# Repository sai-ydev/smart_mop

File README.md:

# Bluetooth-Enabled Smart Mop using the PSOC BLE pioneer kit

A Bluetooth enabled smart mop that tracks liquid refill levels using CapSense Technology.

A detailed writeup is available from [here](https://www.hackster.io/yamanoorsai/bluetooth-enabled-smart-mop-using-the-psoc-ble-pioneer-kit-8d9399).

## Folder structure

1. SmartMop.cydsn - Project workspace for smart mop
2. hardware - PCB design files, Gerbers, and BoM

# Videos

Mobile App Demo

Power Profiling Demo

Smart Mop Demo

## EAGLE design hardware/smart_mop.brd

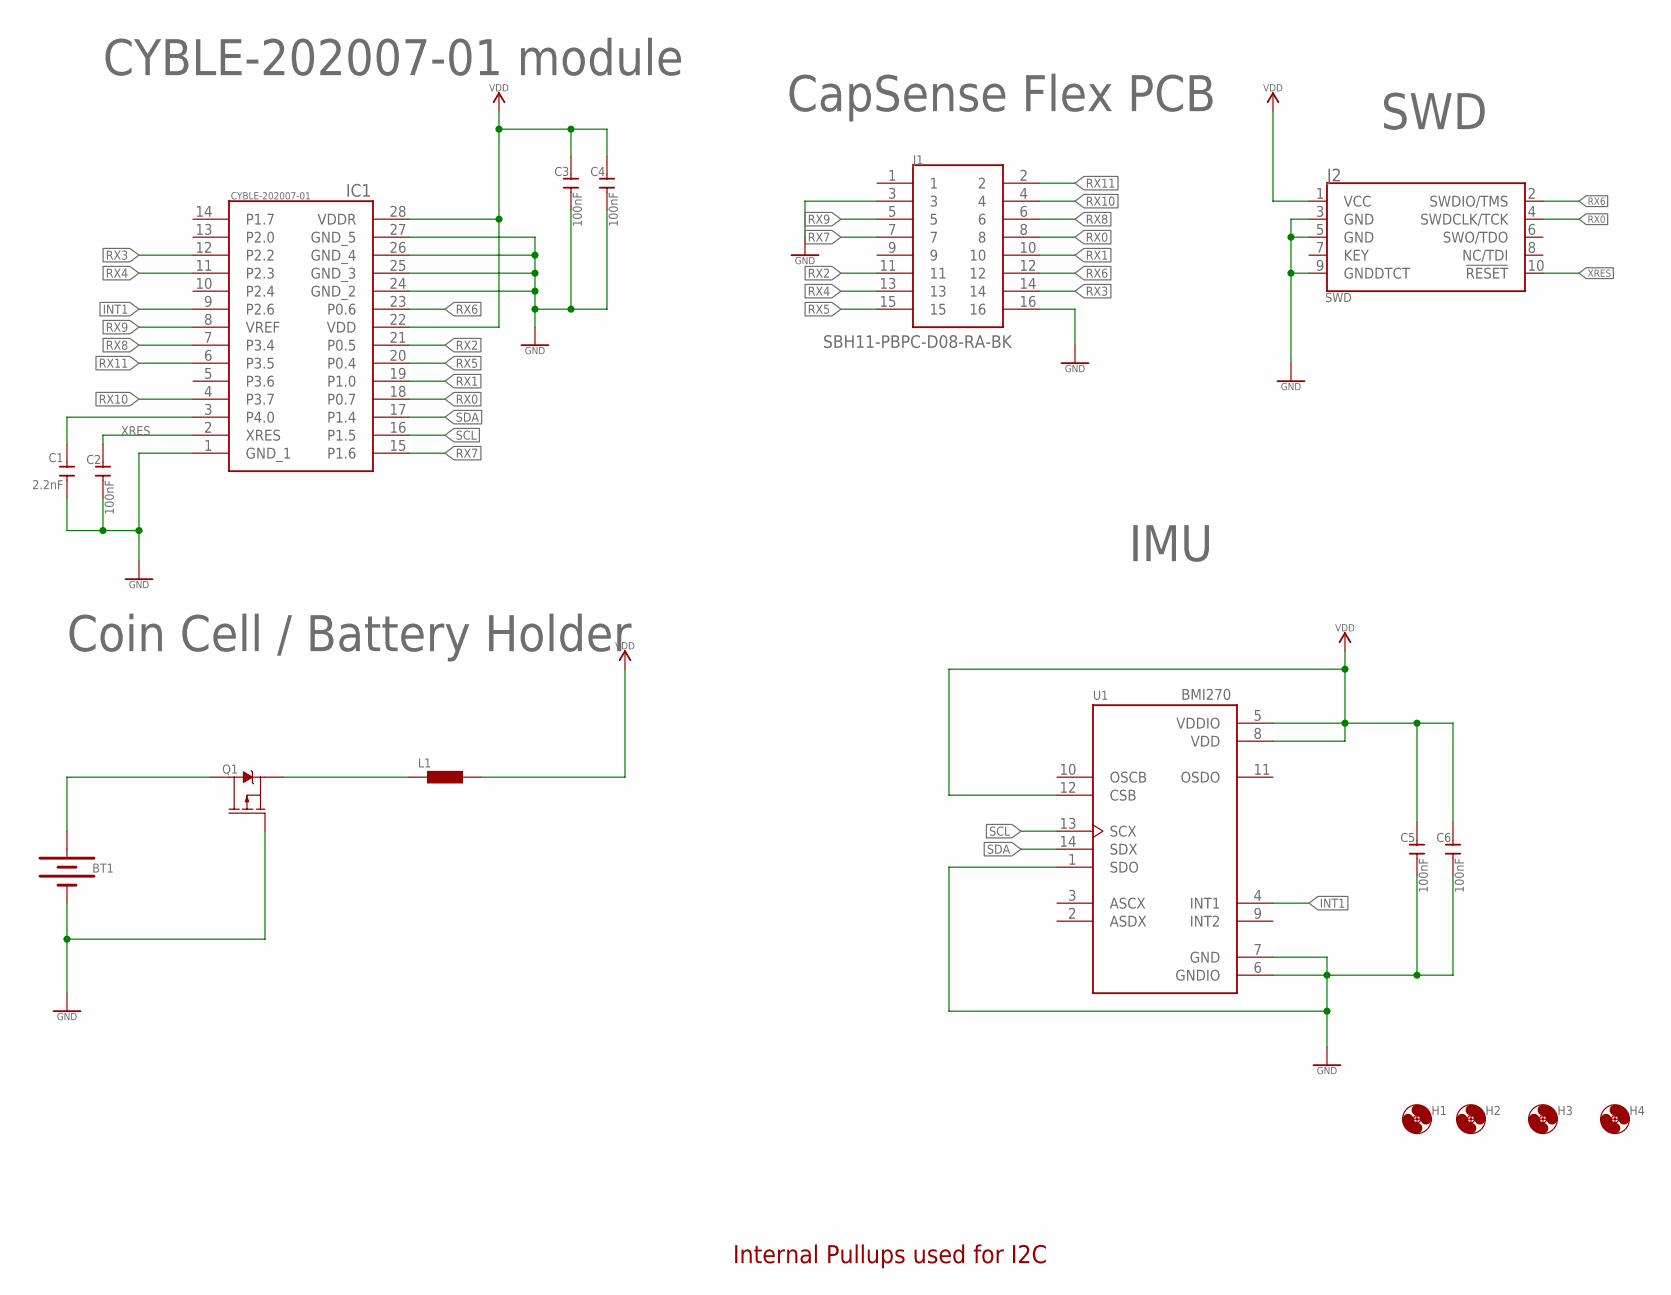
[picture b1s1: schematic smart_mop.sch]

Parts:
BT1: BATTERY-20MM_SMD; BATTCON_20MM
C1: 2.2nF; C0402
C2, C3, C4, C5, C6: 100nF; C0402
H1, H2, H3, H4: MOUNT-HOLE2.8; 2,8
IC1: CYBLE-202007-01; CYBLE20200701
J1: SBH11-PBPC-D08-RA-BK; SHDRRA16W64P254_2X8_2782X910X9
J2: SWD; SAMTECH_FTSH-105-01
L1: BLM15HB121SN1; 0402
Q1: 2.5A/30V/105mΩ; SOT23-3
U1: BMI270; XDCR_BMI270

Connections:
GND: BT1.2 (-), C1.1, C2.1, C3.1, C4.1, C5.1, C6.1, IC1.1 (GND_1), IC1.24 (GND_2), IC1.25 (GND_3), IC1.26 (GND_4), IC1.27 (GND_5), J1.3, J1.16, J2.3 (GND), J2.5 (GND), J2.9 (GNDDTCT), Q1.1 (G), U1.1 (SDO), U1.6 (GNDIO), U1.7 (GND)
INT1: IC1.9 (P2.6), U1.4 (INT1)
unnamed: BT1.1 (+), Q1.3 (D)
unnamed: C1.2, IC1.3 (P4.0)
unnamed: L1.1, Q1.2 (S)
RX0: IC1.18 (P0.7), J1.8, J2.4 (SWDCLK/TCK)
RX1: IC1.19 (P1.0), J1.10
RX2: IC1.21 (P0.5), J1.11
RX3: IC1.12 (P2.2), J1.14
RX4: IC1.11 (P2.3), J1.13
RX5: IC1.20 (P0.4), J1.15
RX6: IC1.23 (P0.6), J1.12, J2.2 (SWDIO/TMS)
RX7: IC1.15 (P1.6), J1.7
RX8: IC1.7 (P3.4), J1.6
RX9: IC1.8 (VREF), J1.5
RX10: IC1.4 (P3.7), J1.4
RX11: IC1.6 (P3.5), J1.2
SCL: IC1.16 (P1.5), U1.13 (SCX)
SDA: IC1.17 (P1.4), U1.14 (SDX)
VDD: C3.2, C4.2, C5.2, C6.2, IC1.22 (VDD), IC1.28 (VDDR), J2.1 (VCC), L1.2, U1.5 (VDDIO), U1.8 (VDD), U1.12 (CSB)
XRES: C2.2, IC1.2 (XRES), J2.10 (!RESET)

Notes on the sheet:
Coin Cell / Battery Holder
CYBLE-202007-01 module
CapSense Flex PCB
IMU
Internal Pullups used for I2C
SWD

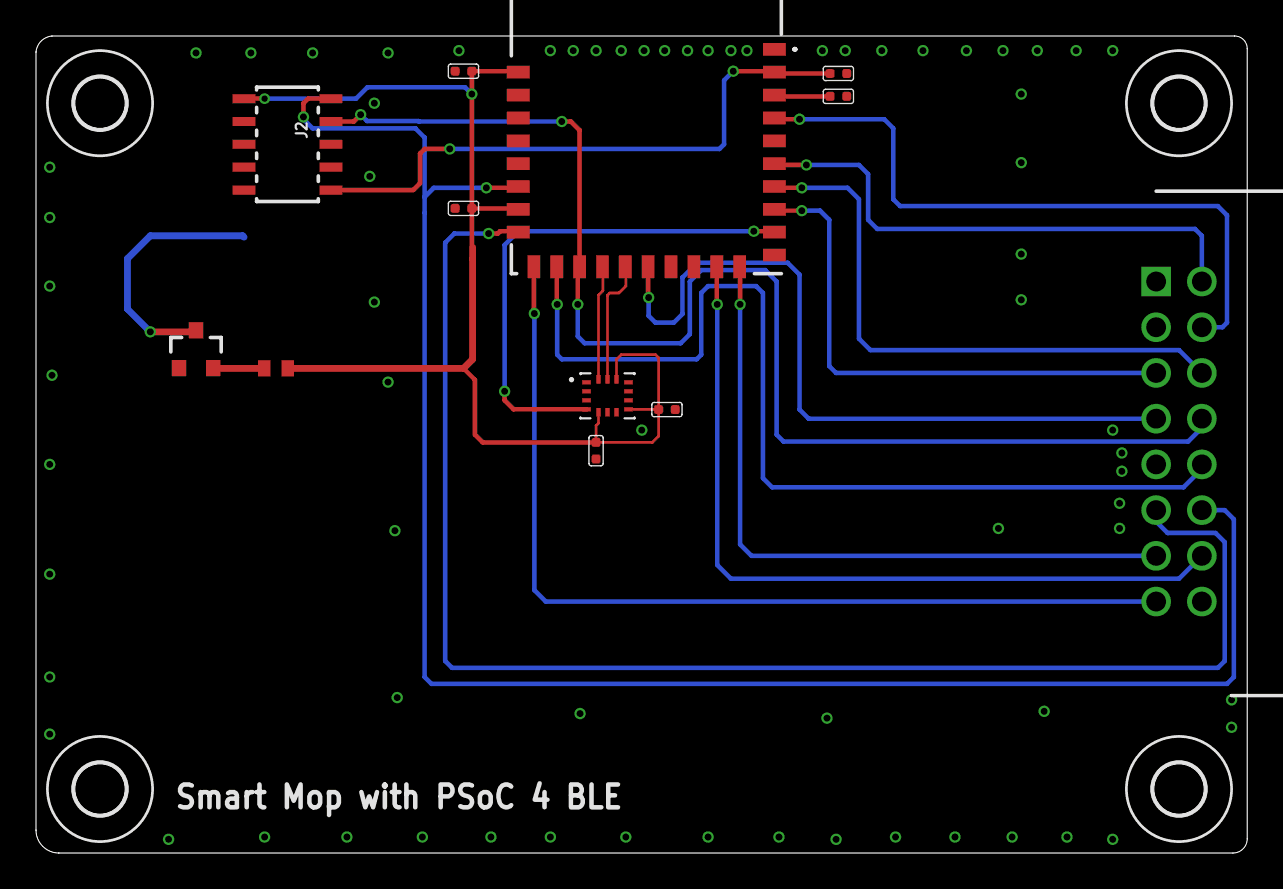
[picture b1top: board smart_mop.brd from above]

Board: 2 copper layers, 67.3 x 45.4 mm, 17 parts (1 on the bottom side), 21 nets.

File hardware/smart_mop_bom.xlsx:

Part | Value | MPN | Cost (USD)
BT1 |  | BATTERY-20MM_SMD | 0.76
C1 | 2.2nF | CERAMIC-2.2NF-50V-10%-X7R(0402) | 2.8819999999999998E-2
C2, C3, C4, C5, C6 | 100nF | CERAMIC-100NF-25V-10%-X7R(0402) | 0.02
IC1 | RF TXRX MOD BT 4.2 TRC ANT SMD | CYBLE-202007-01 | 13.002000000000001
J1 | CONN HEADER R/A 16POS 2.54MM | SBH11-PBPC-D08-RA-BK | 0.40100000000000002
J2 | CONN HEADER SMD 10POS 1.27MM | FTSH-105-01-L-DV-K-P | 2.87
L1 | FERRITE BEAD 300 OHM 0402 1LN | AFBC-Q0402-301-T | 1.78E-2
Q1 | MOSFET P-CH 30V 2.5A SOT-23 | DMG2307L-7 | 9.9000000000000005E-2
U1 | BMI270 | BMI270 | 3.23
 |  | Flex PCB | 5
 |  | Main PCB | 0.33100000000000002
 |  | Total Cost | 25.759620000000002

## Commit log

2023-02-05 Check-in
2023-02-06 Update to design files
2023-02-06 Fixing resets
2023-02-18 Renaming files
2023-02-18 Adding BMI270 drivers
2023-02-19 Working version
2023-02-19 working version commit
2023-02-21 Adopting CE210489
2023-02-26 Hardware files check-in

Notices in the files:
parts and their libraries:
SparkFun-Batteries: Licensing: Creative Commons ShareAlike 4.0 International - https://creativecommons.org/licenses/by-sa/4.0
